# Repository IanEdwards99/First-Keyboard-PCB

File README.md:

# First Keyboard PCB
 Four key keyboard prototype

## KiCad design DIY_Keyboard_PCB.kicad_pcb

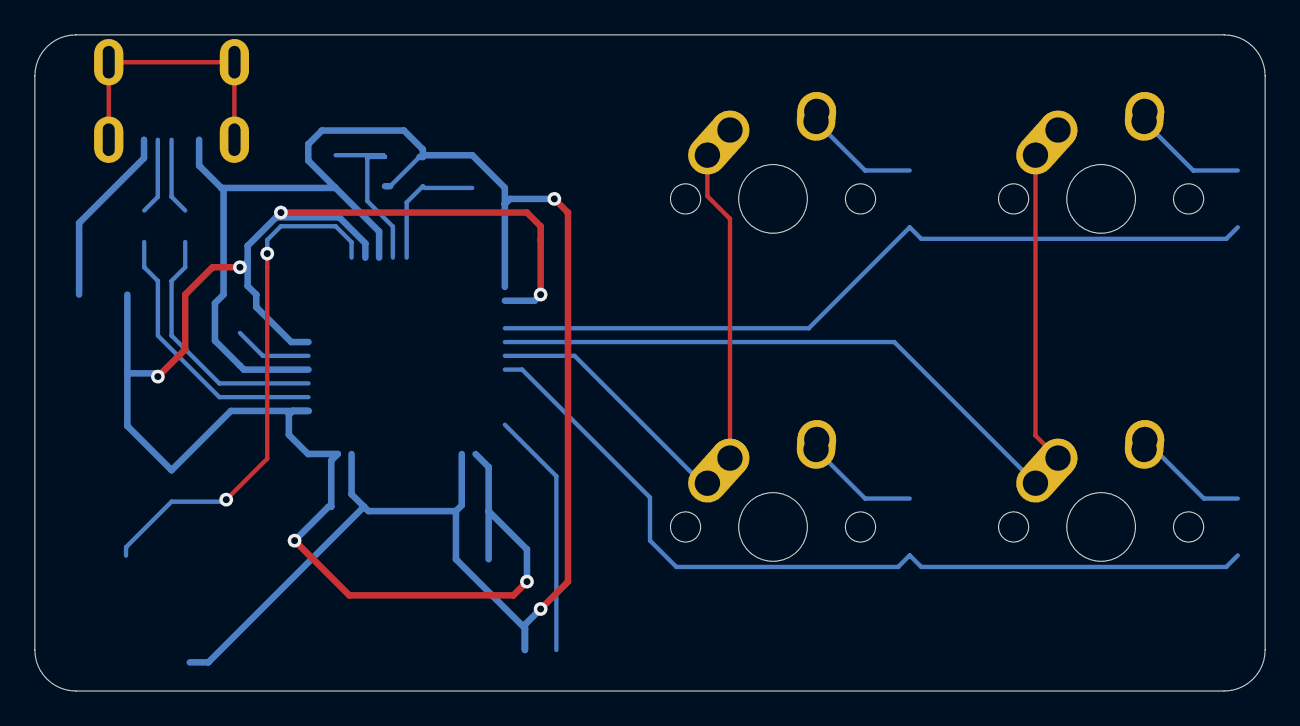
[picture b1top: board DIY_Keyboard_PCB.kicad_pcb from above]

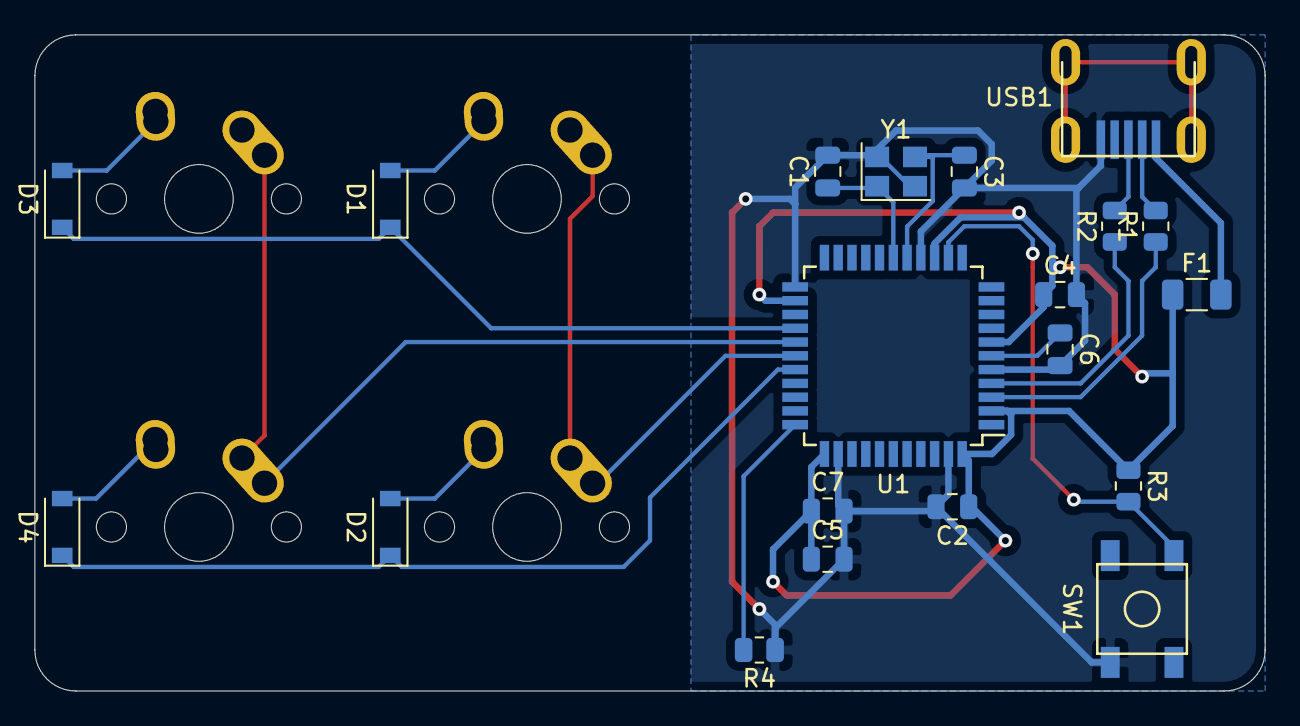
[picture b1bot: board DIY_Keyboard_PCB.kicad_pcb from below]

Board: 2 copper layers, 71.4 x 38.1 mm, 24 parts (20 on the bottom side), 20 nets.

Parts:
C1, C3: 22pF; C_0805_2012Metric
C2, C4, C5: 0.1uF; C_0805_2012Metric
C6: 1uF; C_0805_2012Metric
C7: 10uF; C_0805_2012Metric
D1, D2, D3, D4: D_Small; D_SOD-123
F1: 500mA; Fuse_1206_3216Metric
MX1, MX2, MX3, MX4: MX-NoLED; MX-1U-NoLED
R1, R2: 22; R_0805_2012Metric
R3, R4: 10k; R_0805_2012Metric
SW1: SW_Push; SKQG-1155865
U1: ATmega32U4-AU; TQFP-44_10x10mm_P0.8mm
USB1: Molex-0548190589
Y1: Crystal_GND24_Small; Crystal_SMD_3225-4Pin_3.2x2.5mm

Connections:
+5V: C2.1, C4.1, C5.1, C7.1, F1.1, R3.1, U1.2, U1.7, U1.14, U1.24, U1.34, U1.44
COL0: MX1.1, MX2.1, U1.28
COL1: MX3.1, MX4.1, U1.27
D+: R2.2, USB1.3
D-: R1.2, USB1.4
GND: C1.2, C2.2, C3.2, C4.2, C5.2, C6.2, C7.2, R4.1, SW1.1, U1.5, U1.15, U1.23, U1.35, U1.43, USB1.1, Y1.2, Y1.4
unnamed: C1.1, U1.17, Y1.1
unnamed: C3.1, U1.16, Y1.3
unnamed: C6.1, U1.6
unnamed: D1.2, MX1.2
unnamed: D2.2, MX2.2
unnamed: D3.2, MX3.2
unnamed: D4.2, MX4.2
unnamed: R1.1, U1.3
unnamed: R2.1, U1.4
unnamed: R3.2, SW1.2, U1.13
unnamed: R4.2, U1.33
ROW0: D1.1, D3.1, U1.26
ROW1: D2.1, D4.1, U1.29
VCC: F1.2, USB1.5

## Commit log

2022-03-04 Initialize Project
2022-03-04 Add submodules
2022-03-04 Footprint libraries added
2022-03-04 Schematic done, footprints updated
2022-03-04 Routing and tracing
2022-03-04 Finished - gerbers generated
2022-03-08 Added fiducials and BoM
2022-03-08 Saved changes
